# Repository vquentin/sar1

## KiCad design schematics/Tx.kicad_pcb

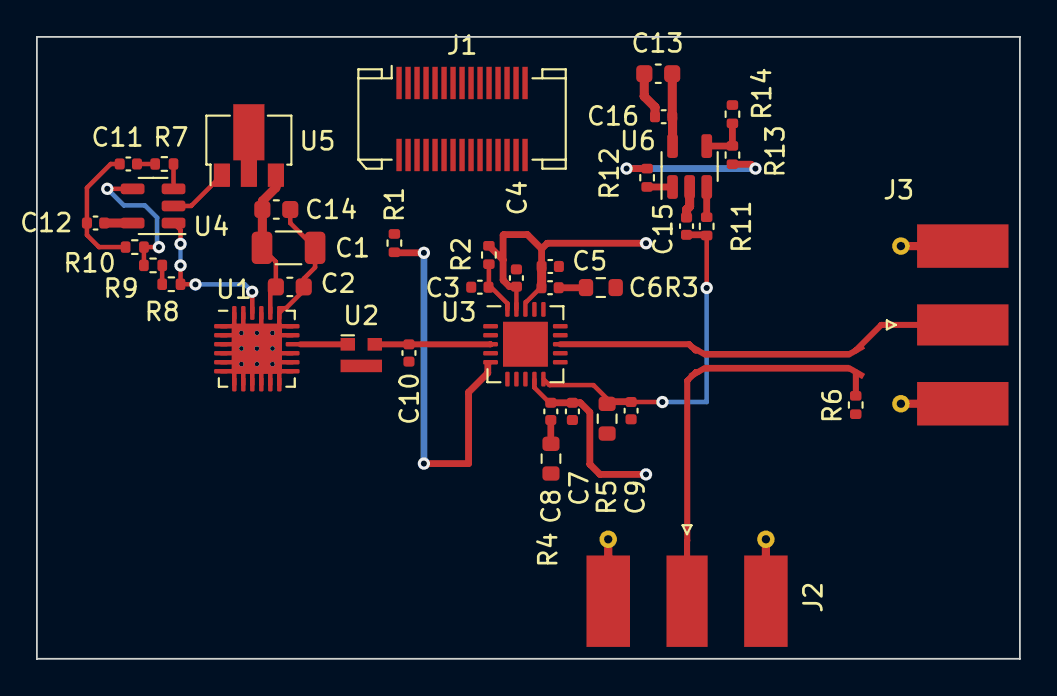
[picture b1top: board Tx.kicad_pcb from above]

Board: 4 copper layers, 54.6 x 34.5 mm, 40 parts (0 on the bottom side), 25 nets.

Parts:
C1: 4.7 uF; C_1206_3216Metric
C2: 10,000 pF; C_0603_1608Metric
C3, C4: 0.1 uF; C_0402_1005Metric
C5, C7: 10 uF; C_0402_1005Metric
C6, C8, C9: 220 pF; C_0402_1005Metric
C10: 0.3 pF; C_0402_1005Metric
C11, C12, C15, C16: 100n; C_0402_1005Metric
C13, C14: 1 uF; C_0603_1608Metric
J1: Conn_02x15_Counter_Clockwise; Molex_SlimStack_52991-0308_2x15_P0.50mm_Vertical
J2, J3: PCB edge; SMA_Molex_73251-1153_EdgeMount_Horizontal
R1: 50k; R_0402_1005Metric
R2: 27; R_0402_1005Metric
R3, R4: 2; R_0603_1608Metric
R5: 27.4k; R_0603_1608Metric
R6: 49.9; R_0402_1005Metric
R7, R11: 100; R_0402_1005Metric
R8, R9, R10, R12, R13, R14: 10k; R_0402_1005Metric
RF1: Coupler; -24 dB coupler 5.5 GHz OSHpark 4 layers
U1: HMC431; QFN-24-1EP_4x4mm_P0.5mm_EP2.8x2.8mm
U2: PAT1220-C-10DB; RF_Attenuator_Susumu_PAT1220
U3: TQP5525; QFN-20-1EP_4x4mm_P0.5mm_EP2.5x2.5mm
U4, U6: TS971ILT; SOT-23-5
U5: MCP1700T-3002E/MB; SOT-89-3

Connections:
+3V3: C13.1, C16.1, J1.2, J1.4, J1.5, J1.6, J1.16, J1.17, U5.2 (VI), U6.5 (V+)
+5V: C4.1, C5.1, C6.1, C7.2, C8.1, J1.8, J1.9, J1.10, J1.12, R2.1, U3.9 (VCC3), U3.18 (VCC3), U3.19 (VCC2)
+10V: C12.1, J1.14, U4.5 (V+)
/3V0: C1.1, C2.1, C14.1, U1.20 (VCC), U5.3 (VO)
/DAC: C11.2, R7.1
/PA_DET: C9.1, C15.2, R5.1, R11.1, U3.10 (DET)
/PA_DET_G: J1.29, R12.1, U6.1
/PA_EN: J1.30, R1.1, U3.5 (PA_EN)
/RF_COUPLER_2: J3.1 (In), RF1.2
/RF_COUPLER_3: R6.1, RF1.3
/RF_COUPLER_4: J2.1 (In), RF1.4
/RF_I_PAMP: C10.1, U2.2, U3.3 (RF_IN)
/RF_O_PAMP: RF1.1, U3.13 (RF_OUT)
/RF_O_VCO: U1.16 (RFOUT), U2.1
/VTUNE: R8.1, U1.22 (VTUNE), U4.1
GND: C1.2, C2.2, C3.2, C4.2, C5.2, C7.1, C9.2, C10.2, C11.1, C12.2, C13.2, C14.2, C15.1, C16.2, J1.1, J1.3, J1.7, J1.11, J1.13, J1.15, J1.18, J1.21, J1.26, J2.2 (Ext), J3.2 (Ext), R1.2, R3.1, R4.1, R5.2, R6.2, R10.2, R14.2, U1.1 (NC), U1.2 (NC), U1.3 (NC), U1.4 (NC), U1.5 (NC), U1.6 (NC), U1.7 (NC), U1.8 (NC), U1.9 (NC), U1.10 (NC), U1.11 (NC), U1.12 (NC), U1.13 (NC), U1.14 (NC), U1.15 (GND), U1.17 (NC), U1.18 (NC), U1.19 (NC), U1.21 (NC), U1.23 (NC), U1.24 (NC), U1.25 (GND), U2.3, U3.1 (GND), U3.2 (GND), U3.4 (GND), U3.11 (GND), U3.12 (GND), U3.14 (GND), U3.15 (GND), U3.16 (GND), U3.17 (GND), U3.21 (GND), U4.2 (V-), U5.1 (GND), U6.2 (V-)
unnamed: C3.1, R2.2, U3.20 (VCC1)
unnamed: C6.2, R3.2
unnamed: C8.2, R4.2
unnamed: R7.2, U4.3 (+)
unnamed: R8.2, R9.1
unnamed: R9.2, R10.1, U4.4 (-)
unnamed: R11.2, U6.3 (+)
unnamed: R12.2, R13.1
unnamed: R13.2, R14.1, U6.4 (-)

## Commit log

2021-09-24 The first commit
2021-09-28 Before footprint assignments check
2021-11-30 Added Rx board
2022-01-04 latest updates
